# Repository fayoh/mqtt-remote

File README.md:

# mqtt-remote
A simple four button remote with an esp8266 that publishes data on mqtt topics

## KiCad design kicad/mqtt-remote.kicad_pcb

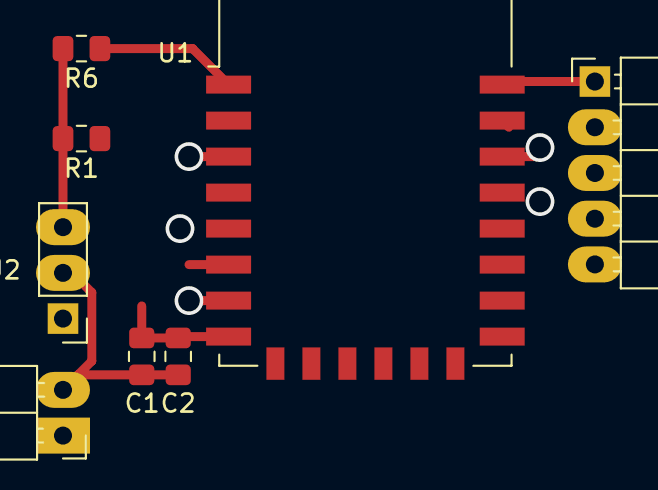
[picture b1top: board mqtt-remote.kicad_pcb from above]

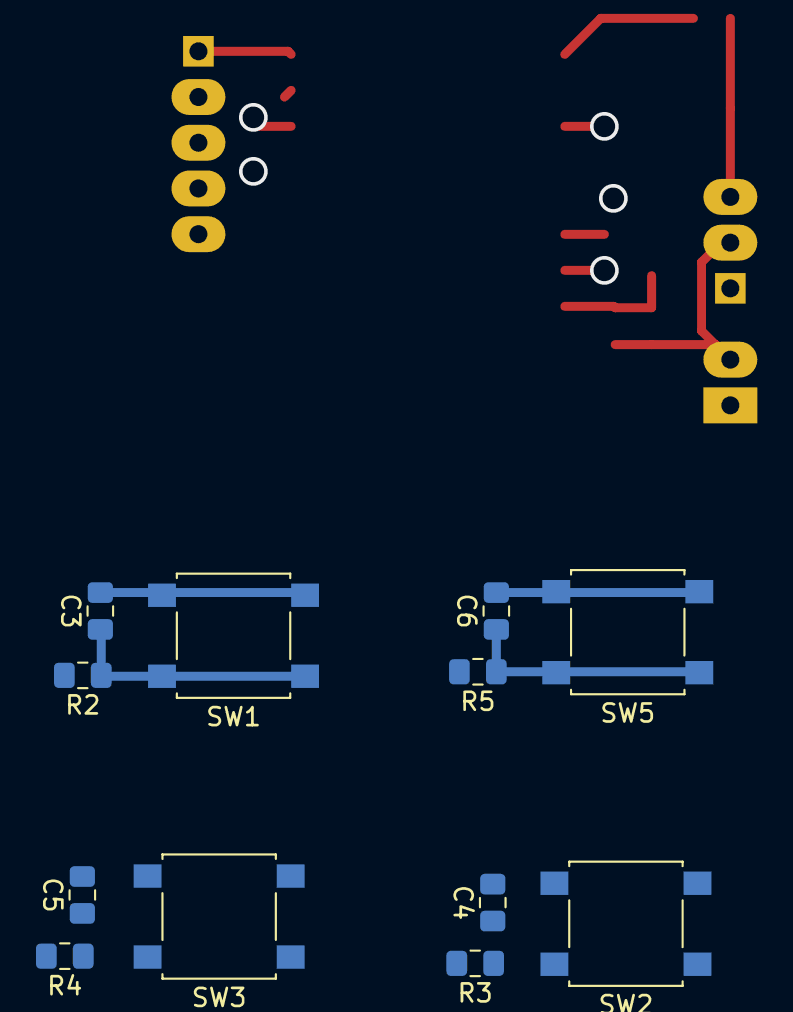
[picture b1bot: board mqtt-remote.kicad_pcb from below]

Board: 2 copper layers, 20 parts (12 on the bottom side), 16 nets.

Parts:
C1, C3, C4, C5, C6: 100n; C_0805_2012Metric_Pad1.15x1.40mm_HandSolder
C2: 47u; C_0805_2012Metric_Pad1.15x1.40mm_HandSolder
J1: Batt; PinHeader_1x02_P2.54mm_Horizontal
J2: Reg; PinHeader_1x03_P2.54mm_Vertical
J3: Conn_01x05; PinHeader_1x05_P2.54mm_Horizontal
R1, R6: 10k; R_0805_2012Metric_Pad1.15x1.40mm_HandSolder
R2, R3, R4, R5: 120; R_0805_2012Metric_Pad1.15x1.40mm_HandSolder
SW1, SW3, SW5: Btn_1; SW_SPST_B3S-1000
SW2: Btn_2; SW_SPST_B3S-1000
U1: ESP-12F; ESP-12E

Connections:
/Btn_1: R2.2, U1.19
/Btn_2: R3.2, U1.20
/Btn_3: R4.2, U1.6
/Btn_4: R5.2, U1.7
/DTS: J3.4, U1.18
/RTS: J3.3, R1.1, U1.3
/RX: J3.2, U1.21
/TX: J3.1, U1.22
/VI: J1.1, J2.1
GND: C1.2, C2.2, C3.2, C4.2, C5.2, C6.2, J1.2, J2.2, J3.5, SW1.2, SW2.2, SW3.2, SW5.2, U1.15
unnamed: C3.1, R2.1, SW1.1
unnamed: C4.1, R3.1, SW2.1
unnamed: C5.1, R4.1, SW3.1
unnamed: C6.1, R5.1, SW5.1
unnamed: R6.1, U1.1
VCC: C1.1, C2.1, J2.3, R1.2, R6.2, U1.8

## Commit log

2020-07-29 Add .whitesource configuration file
2020-07-29 First revision schematic, components random on board
